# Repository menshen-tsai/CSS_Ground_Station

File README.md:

# CSS Ground Station 
Hardware and Firmware/Software for Hand-On Class
---

## 📌 Overview

This repository contains the firmware, hardware configurations, and software components for the CSS Ground Station built using **STM32 microcontrollers** (STM32L432 series). It serves as a practical guide and codebase for hands-on satellite/ground station workshops.

---

## 📁 Repository Structure

├── Ground_Station_L432_SR105U_FLASH_20261008/       # Firmware with SR105U transceiver & Flash memory support<BR>
├── STM32L432_SENDBTN_ENCODER_FLASH_DECODE_20260929/ # Firmware for send button, rotary encoder, & flash decoding<BR>
└── README.md

---

## 🛠️ Hardware & Tools Required

- **MCU:** STM32L432 MCU board
- **Transceiver:** SR105U Module
- **Peripherals:** Rotary Encoder, Push Buttons, SPI Flash Memory
- **IDE/Toolchain:** STM32CubeIDE / Keil uVision
- **Programmer:** ST-LINK V2 / V3

---

## 🚀 Getting Started

### 1. Prerequisites
Ensure you have installed:
- [STM32CubeIDE](https://www.st.com/en/development-tools/stm32cubeide.html) (or your preferred C/C++ toolchain for STM32)
- ST-LINK Drivers

### 2. Cloning the Repository
```bash
git clone [https://github.com/menshen-tsai/CSS_Ground_Station.git](https://github.com/menshen-tsai/CSS_Ground_Station.git)
cd CSS_Ground_Station
```
### 3. Building & Flashing
1. Open STM32CubeIDE.
2. Go to File > Import... > Existing Projects into Workspace.
3. Browse to one of the project folders (e.g., Ground_Station_L432_SR105U_FLASH_20261008).
4. Build the project (Ctrl + B).
5. Connect your STM32 board via ST-LINK and click Run / Debug.

## Image and Video

[📥 Download APRS Decode Video (MP4)](Images/APRS_Decode_DIREWOLF_STM32L432KC_2026-10-20%20132000.mp4)

## 📜 Tech Stack
Primary Language: C (97%+)

Build System: Make / Linker Scripts

Target Platform: STM32L432 Series

## APRS Decoding
The APRS decoding code was based on STM32_APRS by [dragonlock2](https://github.com/dragonlock2/STM32_APRS.git).
The digital filter code is tuned to fulfill the audio signal (AF_OUT) comes from the UHF transceiver (SR105U).

## 👤 Author
menshen-tsai - GitHub Profile

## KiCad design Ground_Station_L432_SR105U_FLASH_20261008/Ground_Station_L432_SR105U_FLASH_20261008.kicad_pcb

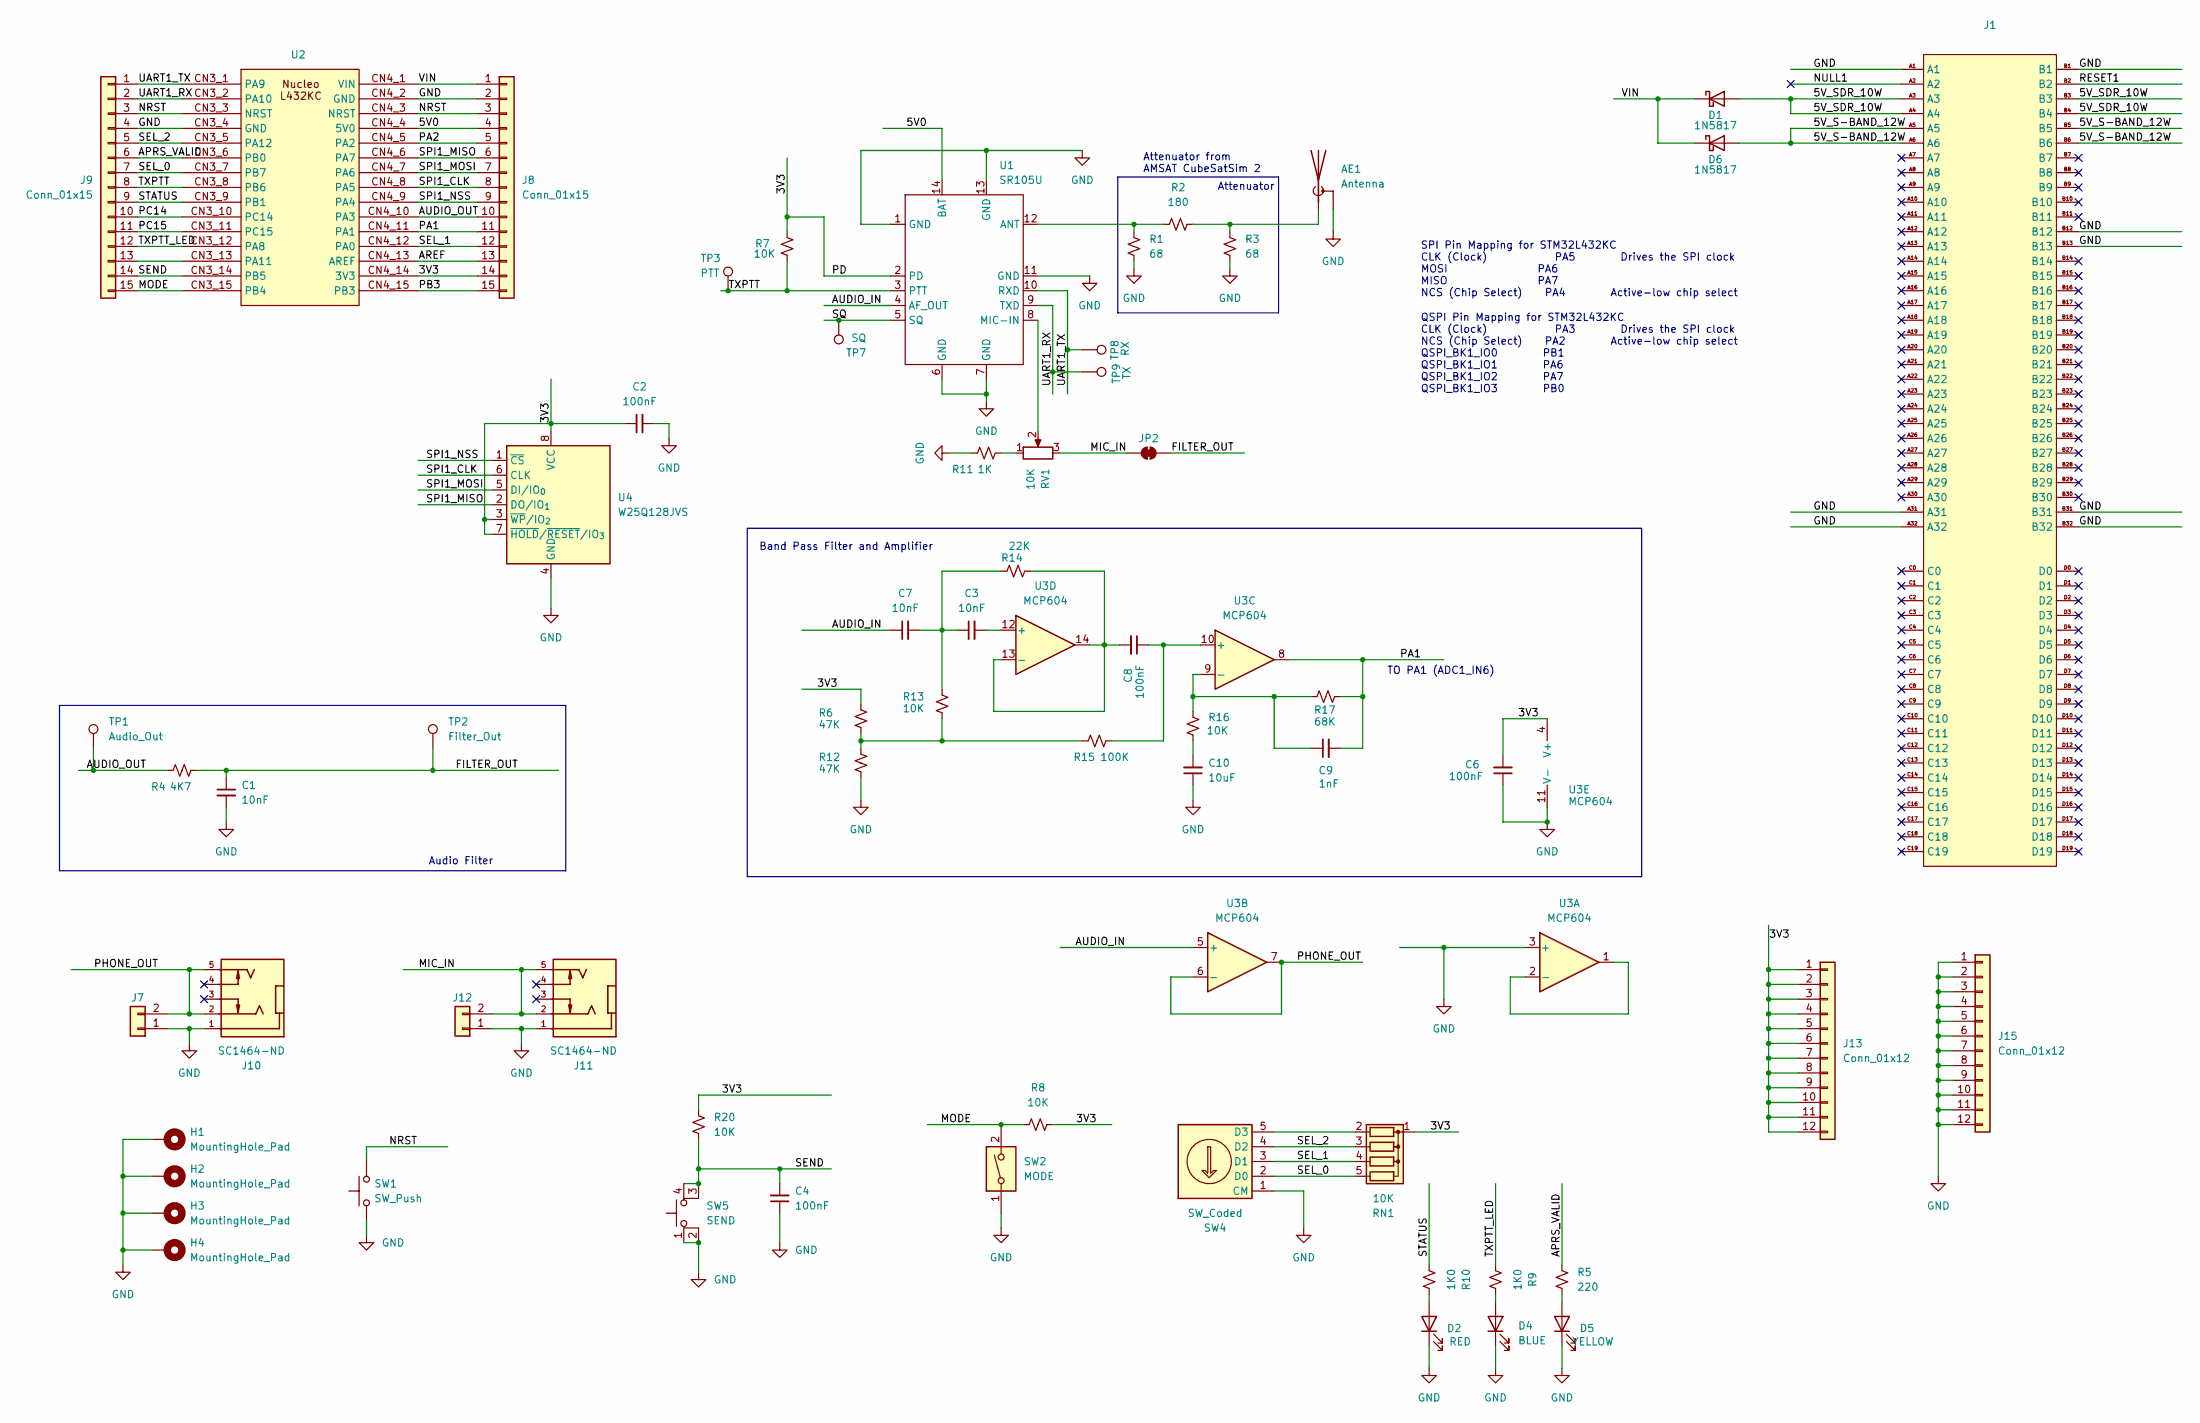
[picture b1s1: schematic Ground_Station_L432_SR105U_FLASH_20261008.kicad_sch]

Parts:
AE1: Antenna; SMA_Amphenol_901-144_Vertical
C1: 10nF; C_0805_2012Metric
C2, C4, C6, C8: 100nF; R_0805_2012Metric
C3, C7: 10nF; R_0805_2012Metric
C9: 1nF; R_0805_2012Metric
C10: 10uF; R_0805_2012Metric
D1, D6: 1N5817; D_DO-41_SOD81_P10.16mm_Horizontal
D2: RED; LED_D5.0mm
D4: BLUE; LED_D5.0mm
D5: YELLOW; LED_D5.0mm
H1, H2, H3, H4: MountingHole_Pad; MountingHole_3.2mm_M3_Pad_Via
J1: PC104_16bit_Connector
J7, J12: SQ; PinHeader_1x02_P2.54mm_Vertical
J8, J9: Conn_01x15; PinHeader_1x15_P2.54mm_Vertical
J10, J11: SC1464-ND; Jack_3.5mm_CUI_SJ1-3525N_Horizontal
J13, J15: Conn_01x12; PinHeader_1x12_P2.54mm_Vertical
JP2: SolderJumper_2_Bridged; SolderJumper-2_P1.3mm_Bridged_Pad1.0x1.5mm
R1, R3: 68; R_1206_3216Metric
R2: 180; R_1206_3216Metric
R4: 4K7; R_0805_2012Metric
R5: 220; R_0805_2012Metric
R6, R12: 47K; R_0805_2012Metric
R7, R8, R13, R16, R20: 10K; R_0805_2012Metric
R9, R10: 1K0; R_0805_2012Metric
R11: 1K; R_0805_2012Metric
R14: 22K; R_0805_2012Metric
R15: 100K; R_0805_2012Metric
R17: 68K; R_0805_2012Metric
RN1: 10K; R_Array_SIP5
RV1: 10K; Potentiometer_Vishay_T73YP_Vertical
SW1: SW_Push; SW_PUSH_1P1T_6x3.5mm_H4.3_APEM_MJTP1243
SW2: MODE; SW_DIP_SPSTx01_Slide_9.78x4.72mm_W7.62mm_P2.54mm
SW4: SW_Coded; DIP_Rotary_BCD
SW5: SEND; SW_PUSH-12mm
TP1: Audio_Out; TestPoint_Pad_D1.5mm
TP2: Filter_Out; TestPoint_Pad_D1.5mm
TP3: PTT; TestPoint_Pad_D1.5mm
TP7: SQ; TestPoint_Pad_D1.5mm
TP8: RX; TestPoint_Pad_D1.5mm
TP9: TX; TestPoint_Pad_D1.5mm
U1: SR105U
U2: MODULE_NUCLEO-L432KC
U3: MCP604
U4: W25Q128JVS; SOIC-8_5.3x5.3mm_P1.27mm

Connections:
/3V3: C2.1, C6.2, J8.14, J13.1, J13.2, J13.3, J13.4, J13.5, J13.6, J13.7, J13.8, J13.9, J13.10, J13.11, J13.12, R6.1, R7.1, R8.1, R20.1, RN1.1 (common), U1.2 (PD), U2.CN4_14 (3V3), U3.4 (V+), U4.3 (~WP/IO_{2}), U4.7 (~HOLD/~RESET/IO_{3}), U4.8 (VCC)
/5V0: J8.4, U1.14 (BAT), U2.CN4_4 (5V0)
/5V_S-BAND_12W: D6.2 (A), J1.A5, J1.A6, J1.B5, J1.B6
/5V_SDR_10W: D1.2 (A), J1.A3, J1.A4, J1.B3, J1.B4
/APRS_VALID: J9.6, R5.2, U2.CN3_6 (PB0)
/AREF: J8.13, U2.CN4_13 (AREF)
/AUDIO_IN: C7.1, U1.4 (AF_OUT), U3.5 (+)
/AUDIO_OUT: J8.10, R4.1, TP1.1 (1_1), U2.CN4_10 (PA3)
/FILTER_OUT: C1.1, JP2.2 (B), R4.2, TP2.1 (1_1)
/MIC_IN: J11.2, J11.5, J12.2, JP2.1 (A), RV1.3
/MODE: J9.15, R8.2, SW2.2, U2.CN3_15 (PB4)
/NRST: J8.3, J9.3, SW1.2, U2.CN3_3 (NRST), U2.CN4_3 (NRST)
/NULL1: J1.A2
/PA1: C9.2, J8.11, R17.2, U2.CN4_11 (PA1), U3.8
/PA2: J8.5, U2.CN4_5 (PA2)
/PB3: J8.15, U2.CN4_15 (PB3)
/PC14: J9.10, U2.CN3_10 (PC14)
/PC15: J9.11, U2.CN3_11 (PC15)
/PHONE_OUT: J7.2, J10.2, J10.5, U3.6 (-), U3.7
/RESET1: J1.B2
/SEL_0: J9.7, RN1.5 (R4), SW4.2 (D0), U2.CN3_7 (PB7)
/SEL_1: J8.12, RN1.4 (R3), SW4.3 (D1), U2.CN4_12 (PA0)
/SEL_2: J9.5, RN1.3 (R2), SW4.4 (D2), U2.CN3_5 (PA12)
/SEND: C4.2, J9.14, R20.2, SW5.3 (K), SW5.4 (A), U2.CN3_14 (PB5)
/SPI1_CLK: J8.8, U2.CN4_8 (PA5), U4.6 (CLK)
/SPI1_MISO: J8.6, U2.CN4_6 (PA7), U4.2 (DO/IO_{1})
/SPI1_MOSI: J8.7, U2.CN4_7 (PA6), U4.5 (DI/IO_{0})
/SPI1_NSS: J8.9, U2.CN4_9 (PA4), U4.1 (~CS)
/SQ: TP7.1 (1_1), U1.5 (SQ)
/STATUS: J9.9, R10.2, U2.CN3_9 (PB1)
/TXPTT: J9.8, R7.2, TP3.1 (1_1), U1.3 (PTT), U2.CN3_8 (PB6)
/TXPTT_LED: J9.12, R9.2, U2.CN3_12 (PA8)
/UART1_RX: J9.2, TP9.1 (1_1), U1.9 (TXD), U2.CN3_2 (PA10)
/UART1_TX: J9.1, TP8.1 (1_1), U1.10 (RXD), U2.CN3_1 (PA9)
/VIN: D1.1 (K), D6.1 (K), J8.1, U2.CN4_1 (VIN)
GND: AE1.2 (Shield), C1.2, C2.2, C4.1, C6.1, C10.1, D2.1 (K), D4.1 (K), D5.1 (K), H1.1 (1_1), H2.1 (1_1), H3.1 (1_1), H4.1 (1_1), J1.A1, J1.A31, J1.A32, J1.B1, J1.B12, J1.B13, J1.B31, J1.B32, J7.1, J8.2, J9.4, J10.1, J11.1, J12.1, J15.1, J15.2, J15.3, J15.4, J15.5, J15.6, J15.7, J15.8, J15.9, J15.10, J15.11, J15.12, R1.2, R3.2, R11.1, R12.2, SW1.1, SW2.1, SW4.1 (CM), SW5.1, SW5.2, U1.1 (GND), U1.6 (GND), U1.7 (GND), U1.11 (GND), U1.13 (GND), U2.CN3_4 (GND), U2.CN4_2 (GND), U3.3 (+), U3.11 (V-), U4.4 (GND)
unnamed: AE1.1 (A), R2.2, R3.1
unnamed: C3.1, C7.2, R13.1, R14.1
unnamed: C10.2, R16.2
unnamed: D2.2 (A), R10.1
unnamed: D4.2 (A), R9.1
unnamed: D5.2 (A), R5.1
unnamed: J9.13, U2.CN3_13 (PA11)
unnamed: R11.2, RV1.1
unnamed: R6.2, R12.1, R13.2, R15.1
unnamed: RN1.2 (R1), SW4.5 (D3)
unnamed: R1.1, R2.1, U1.12 (ANT)
unnamed: RV1.2, U1.8 (MIC-IN)
unnamed: U3.1, U3.2 (-)
unnamed: C8.1, R15.2, U3.10 (+)
unnamed: C9.1, R16.1, R17.1, U3.9 (-)
unnamed: C3.2, U3.12 (+)
unnamed: C8.2, R14.2, U3.13 (-), U3.14

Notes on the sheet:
Attenuator
QSPI Pin Mapping for STM32L432KC CLK (Clock) PA3 Drives the SPI clock NCS (Chip Select) PA2 Active-low chip select QSPI_BK1_IO0 PB1 QSPI_BK1_IO1 PA6 QSPI_BK1_IO2 PA7 QSPI_BK1_IO3 PB0
TO PA1 (ADC1_IN6)
Band Pass Filter and Amplifier
Attenuator from AMSAT CubeSatSim 2
SPI Pin Mapping for STM32L432KC CLK (Clock) PA5 Drives the SPI clock MOSI PA6 MISO PA7 NCS (Chip Select) PA4 Active-low chip select
Audio Filter

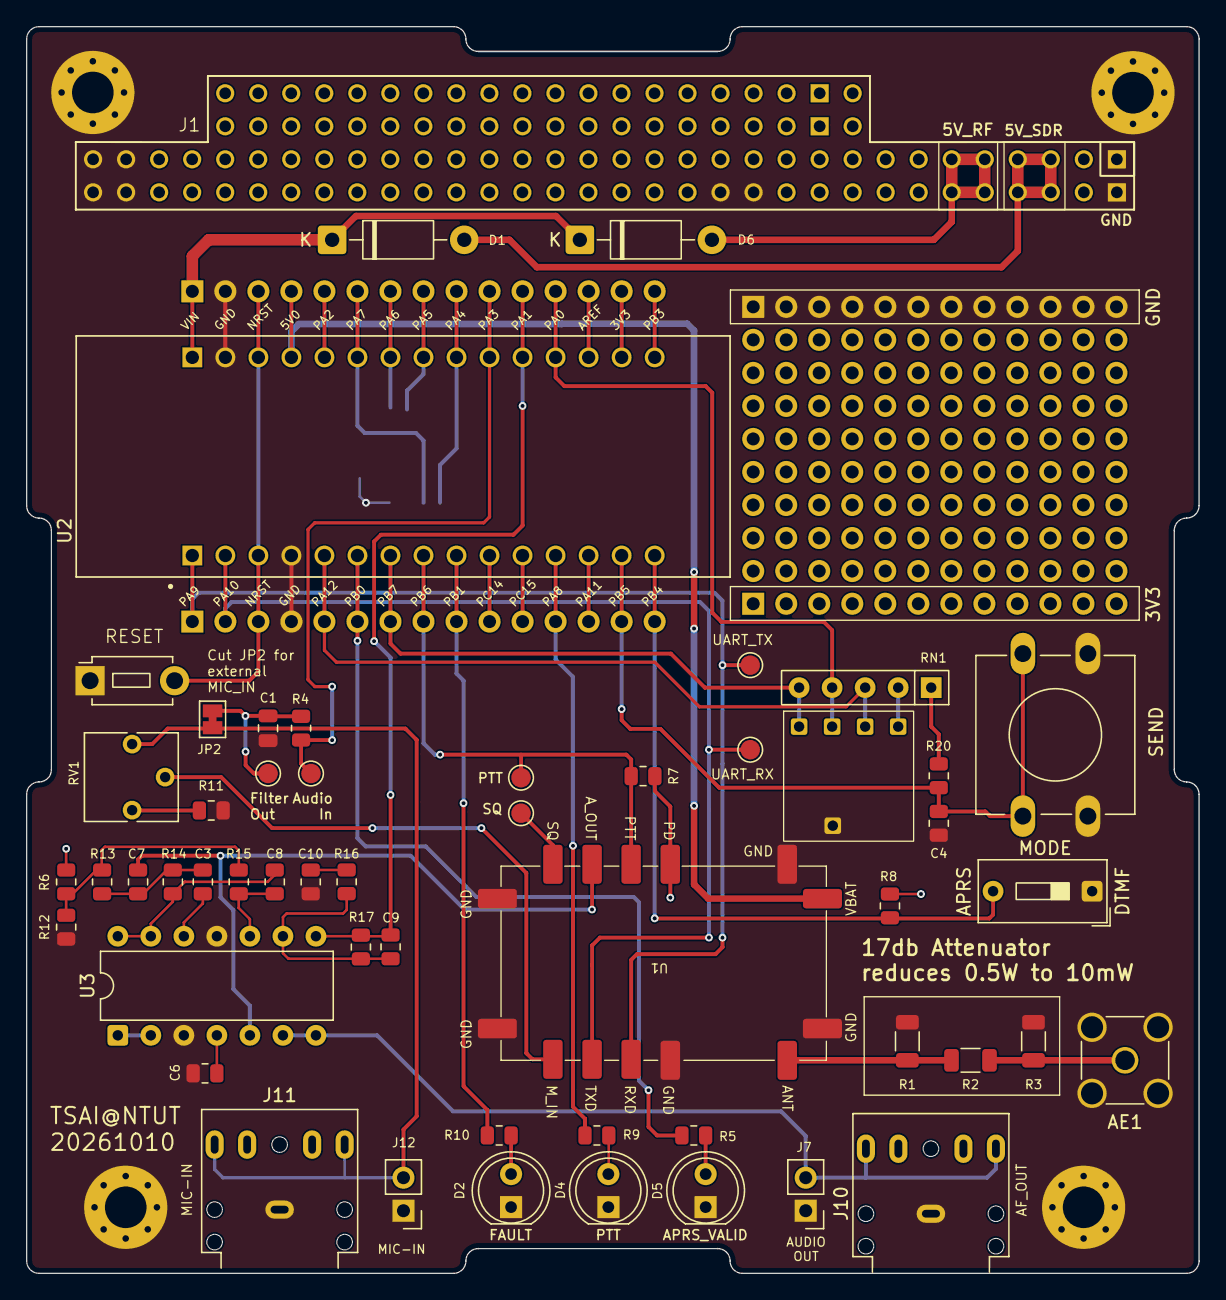
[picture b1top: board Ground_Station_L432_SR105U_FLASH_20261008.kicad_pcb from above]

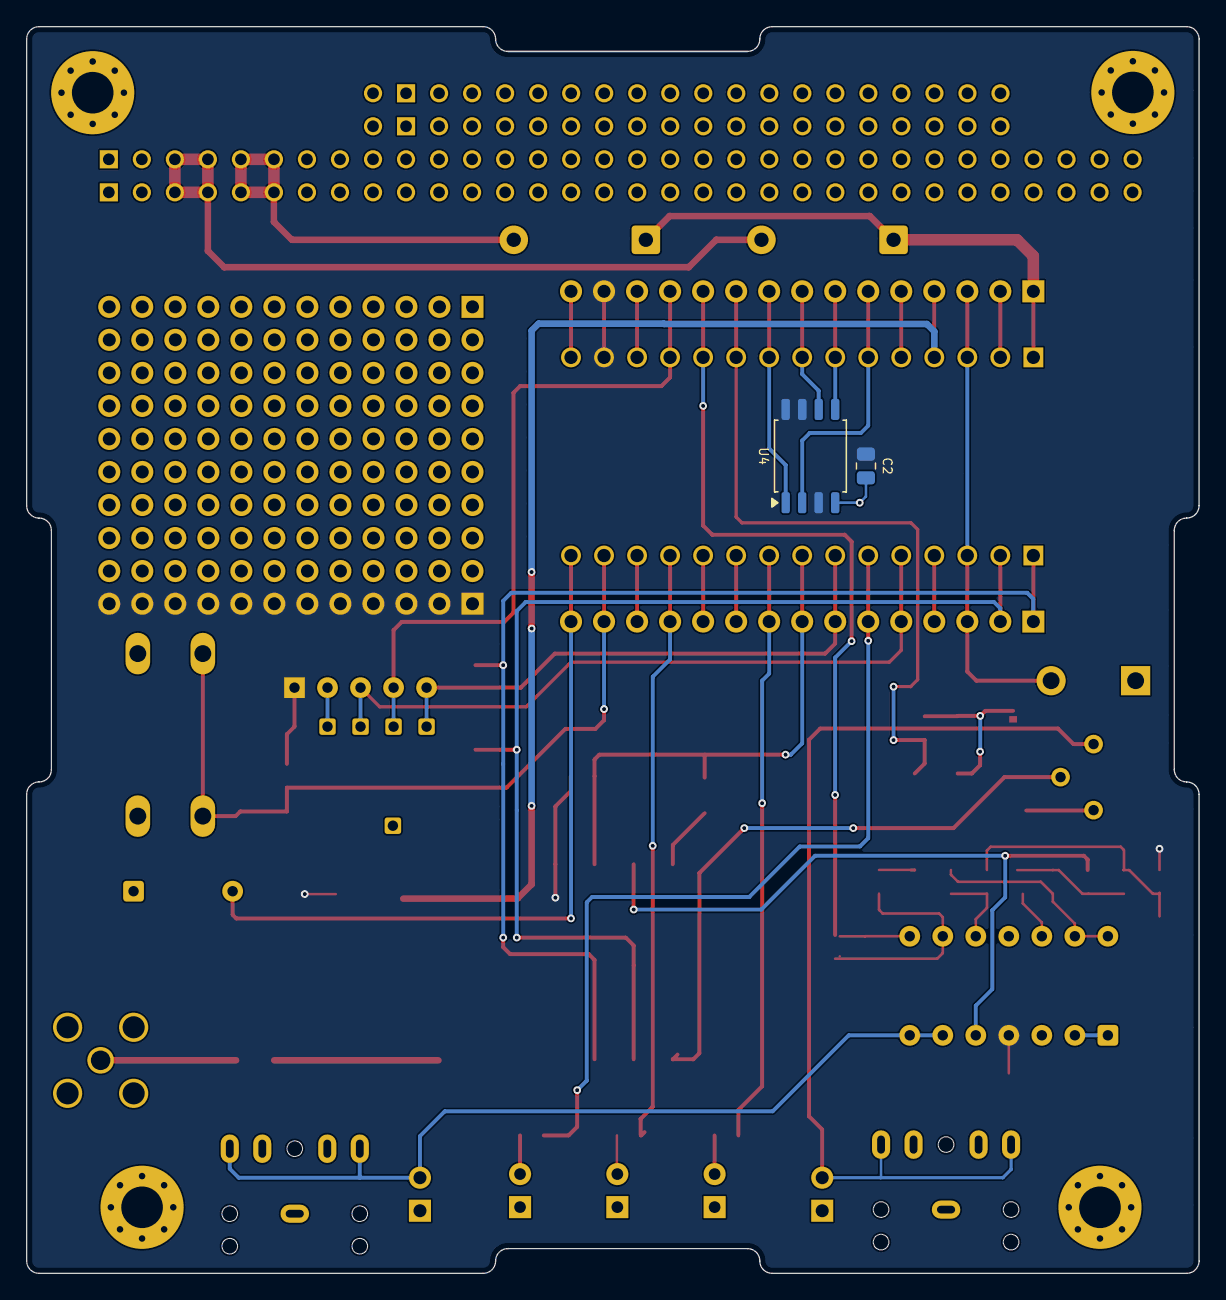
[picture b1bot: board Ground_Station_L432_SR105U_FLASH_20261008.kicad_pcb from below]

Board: 2 copper layers, 90.2 x 95.9 mm, 63 parts (2 on the bottom side), 51 nets.

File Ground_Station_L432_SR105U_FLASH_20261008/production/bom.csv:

Designator,Footprint,Quantity,Value,LCSC Part #
AE1,SMA_Amphenol_901-144_Vertical,1,Antenna,
"C1, C3, C7",0805,3,10nF,
C10,0805,1,10uF,
"C2, C4, C6, C8",0805,4,100nF,
C9,0805,1,1nF,
"D1, D6",D_DO-41_SOD81_P10.16mm_Horizontal,2,1N5817,
D2,LED_D5.0mm,1,RED,
D4,LED_D5.0mm,1,BLUE,
D5,LED_D5.0mm,1,YELLOW,
J1,PC104_16bit_Connector,1,~,
"J10, J11",Jack_3.5mm_CUI_SJ1-3525N_Horizontal,2,SC1464-ND,
"J12, J7",PinHeader_1x02_P2.54mm_Vertical,2,SQ,
"J13, J15",PinHeader_1x12_P2.54mm_Vertical,2,Conn_01x12,
"J8, J9",PinHeader_1x15_P2.54mm_Vertical,2,Conn_01x15,
"R1, R3",1206,2,68,
"R10, R9",0805,2,1K0,
R11,0805,1,1K,
"R12, R6",0805,2,47K,
"R13, R16, R20, R7, R8",0805,5,10K,
R14,0805,1,22K,
R15,0805,1,100K,
R17,0805,1,68K,
R2,1206,1,180,
R4,0805,1,4K7,
R5,0805,1,220,
RN1,R_Array_SIP5,1,10K,
RV1,Potentiometer_Vishay_T73YP_Vertical,1,10K,
SW1,SW_PUSH_1P1T_6x3.5mm_H4.3_APEM_MJTP1243,1,SW_Push,
SW2,SW_DIP_SPSTx01_Slide_9.78x4.72mm_W7.62mm_P2.54mm,1,MODE,
SW4,DIP_Rotary_BCD,1,SW_Coded,
SW5,SW_PUSH-12mm,1,SEND,
TP1,TestPoint_Pad_D1.5mm,1,Audio_Out,
TP2,TestPoint_Pad_D1.5mm,1,Filter_Out,
TP3,TestPoint_Pad_D1.5mm,1,PTT,
TP7,TestPoint_Pad_D1.5mm,1,SQ,
TP8,TestPoint_Pad_D1.5mm,1,RX,
TP9,TestPoint_Pad_D1.5mm,1,TX,
U1,SR105U,1,SR105U,
U2,MODULE_NUCLEO-L432KC,1,~,
U3,DIP-14_W7.62mm,1,MCP604,
U4,SOIC-8_5.3x5.3mm_P1.27mm,1,W25Q128JVS,

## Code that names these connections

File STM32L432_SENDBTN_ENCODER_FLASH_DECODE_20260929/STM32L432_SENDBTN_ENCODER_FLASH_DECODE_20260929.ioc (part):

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Mcu.Name=STM32L432K(B-C)Ux
Mcu.Package=UFQFPN32
Mcu.UserName=STM32L432KCUx
PA0.GPIOParameters=GPIO_Label
PA0.GPIO_Label=SELECT_1
PA0.Signal=GPIO_Input
PA1.Signal=ADCx_IN6
PA10.Mode=Asynchronous
PA10.Signal=USART1_RX
PA12.GPIOParameters=GPIO_Label
PA12.GPIO_Label=SELECT_2
PA12.Signal=GPIO_Input
PA13\ (JTMS-SWDIO).GPIOParameters=GPIO_Label
PA13\ (JTMS-SWDIO).GPIO_Label=SWDIO
PA13\ (JTMS-SWDIO).Mode=Serial_Wire
PA13\ (JTMS-SWDIO).Signal=SYS_JTMS-SWDIO
PA14\ (JTCK-SWCLK).GPIOParameters=GPIO_Label
PA14\ (JTCK-SWCLK).GPIO_Label=SWCLK
PA14\ (JTCK-SWCLK).Mode=Serial_Wire
PA14\ (JTCK-SWCLK).Signal=SYS_JTCK-SWCLK
PA15\ (JTDI).GPIOParameters=GPIO_Label
PA15\ (JTDI).GPIO_Label=VCP_RX
PA15\ (JTDI).Mode=Asynchronous
PA15\ (JTDI).Signal=USART2_RX
PA2.GPIOParameters=GPIO_Label
PA2.GPIO_Label=VCP_TX
PA2.Mode=Asynchronous
PA2.Signal=USART2_TX
PA3.Mode=Follower-DAC_OUT1-INP
PA3.Signal=OPAMP1_VOUT
PA4.GPIOParameters=GPIO_Label
PA4.GPIO_Label=SPI_NSS
PA4.Signal=GPIO_Output
PA5.Mode=Full_Duplex_Master
PA5.Signal=SPI1_SCK
PA6.Mode=Full_Duplex_Master
PA6.Signal=SPI1_MISO
PA7.Mode=Full_Duplex_Master
PA7.Signal=SPI1_MOSI
PA8.GPIOParameters=GPIO_Label
PA8.GPIO_Label=TX_PTT_LED
PA8.Signal=GPIO_Output
PA9.Mode=Asynchronous
PA9.Signal=USART1_TX
PB0.GPIOParameters=GPIO_Label
PB0.GPIO_Label=APRS_VALID
PB0.Signal=GPIO_Output
PB1.GPIOParameters=GPIO_Label
PB1.GPIO_Label=STATUS
PB1.Signal=GPIO_Output
PB3\ (JTDO-TRACESWO).GPIOParameters=GPIO_Label
PB3\ (JTDO-TRACESWO).GPIO_Label=LD3 [Green]
PB3\ (JTDO-TRACESWO).Signal=GPIO_Output
PB4\ (NJTRST).GPIOParameters=GPIO_Label
PB4\ (NJTRST).GPIO_Label=MODE
PB4\ (NJTRST).Signal=GPIO_Input
PB5.GPIOParameters=GPIO_Label,GPIO_ModeDefaultEXTI
PB5.GPIO_Label=SEND_BTN
PB5.GPIO_ModeDefaultEXTI=GPIO_MODE_IT_FALLING
PB5.Signal=GPXTI5
PB6.GPIOParameters=GPIO_Label
PB6.GPIO_Label=TX_PTT
PB6.Signal=GPIO_Output
PB7.GPIOParameters=GPIO_Label
PB7.GPIO_Label=SELECT_0
PB7.Signal=GPIO_Input
PC14-OSC32_IN\ (PC14).Mode=LSE-External-Oscillator
PC14-OSC32_IN\ (PC14).Signal=RCC_OSC32_IN
PC15-OSC32_OUT\ (PC15).Mode=LSE-External-Oscillator
PC15-OSC32_OUT\ (PC15).Signal=RCC_OSC32_OUT
RCC.HSE_VALUE=8000000
RCC.SYSCLKFreq_VALUE=80000000
RCC.SYSCLKSource=RCC_SYSCLKSOURCE_PLLCLK
board=NUCLEO-L432KC
boardIOC=true
